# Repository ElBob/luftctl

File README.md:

# luftctl

Small ESP32-C3 controller board to power two 12V PWM fans from a single USB-C plug.

## hardware

Schematic and PCB design can be found in [`hardware/`](hardware/). It is a KiCAD 6 project.

The schematic is available as [a PDF](schematic.pdf).

For hand-soldering, you can use the [interactive BOM viewer](hardware/ibom.html).

## firmware

### micropython

The first simple test just loops through {`5V/off`, `5V/on`, `12V/off`, `12V/on`} with every button press.

Download MicroPython from [micropython.org/download/esp32c3-usb/](https://micropython.org/download/esp32c3-usb/) and flash it with:

```
esptool.py --chip esp32c3 --port /dev/ttyACM0 erase_flash
esptool.py --chip esp32c3 --port /dev/ttyACM0 --baud 460800 write_flash -z 0x0 esp32c3-*.bin
```

Then install a virtualenv with `adafruit-ampy` and upload the [`main.py`](main.py):

```
ampy -p /dev/ttyACM0 put main.py
ampy -p /dev/ttyACM0 reset --hard
```

The red LED will blink upon every state change.

### esphome

Since the ESP32-C3 is easily supported by ESPHome, you can also add it in your HomeAssistant automation using the [provided example YAML](esphome/luftctl.yaml).

## images

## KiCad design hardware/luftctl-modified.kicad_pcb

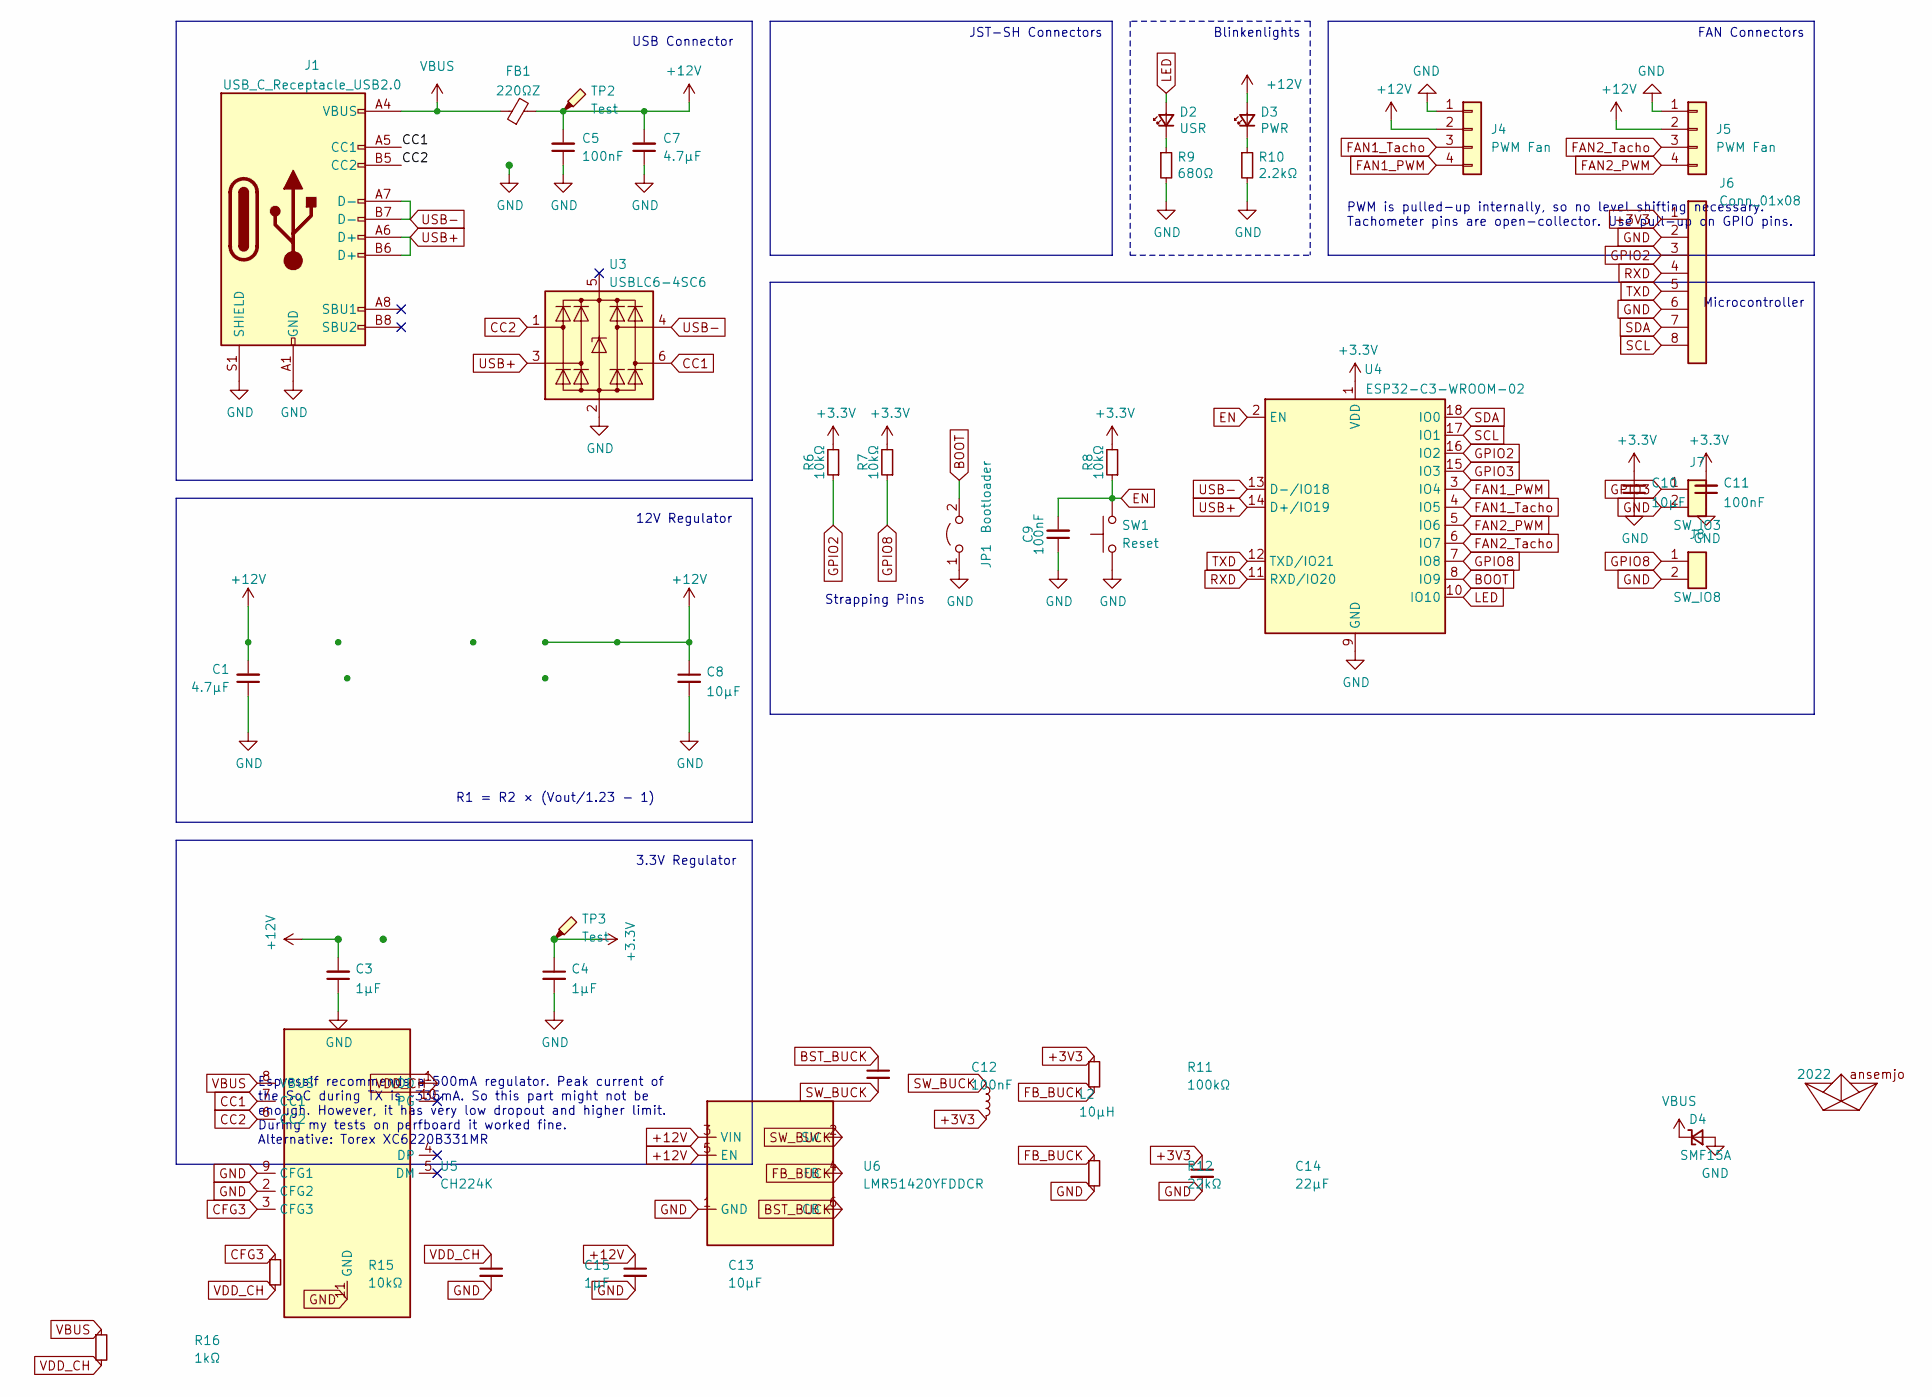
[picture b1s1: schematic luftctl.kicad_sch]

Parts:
A1: 2022; ahoi
C1, C7: 4.7µF; C_0805_2012Metric_Pad1.18x1.45mm_HandSolder
C3, C4, C15: 1µF; C_0805_2012Metric_Pad1.18x1.45mm_HandSolder
C5, C9, C11, C12: 100nF; C_0805_2012Metric_Pad1.18x1.45mm_HandSolder
C8, C10, C13: 10µF; C_0805_2012Metric_Pad1.18x1.45mm_HandSolder
C14: 22µF; C_0805_2012Metric_Pad1.18x1.45mm_HandSolder
D2: USR; LED_0805_2012Metric_Pad1.15x1.40mm_HandSolder
D3: PWR; LED_0805_2012Metric_Pad1.15x1.40mm_HandSolder
D4: SMF15A; D_SOD-123F
FB1: 220ΩZ; L_0805_2012Metric_Pad1.15x1.40mm_HandSolder
J1: USB_C_Receptacle_USB2.0; USB_C_Receptacle_HRO_TYPE-C-31-M-12
J4, J5: PWM Fan; FanPinHeader_1x04_P2.54mm_Vertical
J6: Conn_01x08; PinHeader_1x08_P2.54mm_Vertical
J7: SW_IO3; PinHeader_1x02_P2.54mm_Vertical
J8: SW_IO8; PinHeader_1x02_P2.54mm_Vertical
JP1: Bootloader; SW_SPST_TS-1088-xR020
L2: 10µH; L_Bourns_SRN6045TA
R6, R7, R8, R15: 10kΩ; R_0805_2012Metric_Pad1.20x1.40mm_HandSolder
R9: 680Ω; R_0805_2012Metric_Pad1.20x1.40mm_HandSolder
R10: 2.2kΩ; R_0805_2012Metric_Pad1.20x1.40mm_HandSolder
R11: 100kΩ; R_0805_2012Metric_Pad1.20x1.40mm_HandSolder
R12: 22kΩ; R_0805_2012Metric_Pad1.20x1.40mm_HandSolder
R16: 1kΩ; R_0805_2012Metric_Pad1.20x1.40mm_HandSolder
SW1: Reset; SW_SPST_TS-1088-xR020
TP2, TP3: Test; TestPoint_THTPad_D1.5mm_Drill0.7mm
U3: USBLC6-4SC6; SOT-23-6; MPN USBLC6-4SC6; Digi-Key_PN 497-4492-1-ND
U4: ESP32-C3-WROOM-02; ESP-WROOM-02
U5: CH224K; SSOP-10-1EP_3.9x4.9mm_P1mm_EP2.1x3.3mm
U6: LMR51420YFDDCR; SOT-23-6

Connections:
+12V: C1.2, C3.2, C5.2, C7.2, C8.1, C13.1, D3.2 (A), FB1.2, J4.2, J5.2, TP2.1, U6.3 (VIN), U6.5 (EN)
BOOT: JP1.2 (B), U4.8 (IO9)
BST_BUCK: C12.1, U6.6 (CB)
CC1: J1.A5 (CC1), U3.6 (I/O4), U5.7 (CC1)
CC2: J1.B5 (CC2), U3.1 (I/O1), U5.6 (CC2)
CFG3: R15.1, U5.3 (CFG3)
EN: C9.2, R8.1, SW1.2, U4.2 (EN)
FAN1_PWM: J4.4, U4.3 (IO4)
FAN1_Tacho: J4.3, U4.4 (IO5)
FAN2_PWM: J5.4, U4.5 (IO6)
FAN2_Tacho: J5.3, U4.6 (IO7)
FB_BUCK: R11.2, R12.1, U6.4 (FB)
GND: C1.1, C3.1, C4.2, C5.1, C7.1, C8.2, C9.1, C10.1, C11.1, C13.2, C14.2, C15.2, D4.2 (A), J1.A1 (GND), J1.A12 (GND), J1.B1 (GND), J1.B12 (GND), J1.S1 (SHIELD), J4.1, J5.1, J6.2, J6.6, J7.2, J8.2, JP1.1 (A), R9.2, R10.2, R12.2, SW1.1, U3.2 (GND), U4.9 (GND), U4.19 (GND), U5.2 (CFG2), U5.9 (CFG1), U5.11 (GND), U6.1 (GND)
GPIO2: J6.3, R6.1, U4.16 (IO2)
GPIO3: J7.1, U4.15 (IO3)
GPIO8: J8.1, R7.1, U4.7 (IO8)
LED: D2.2 (A), U4.10 (IO10)
unnamed: D2.1 (K), R9.1
unnamed: D3.1 (K), R10.1
RXD: J6.4, U4.11 (RXD/IO20)
SCL: J6.8, U4.17 (IO1)
SDA: J6.7, U4.18 (IO0)
SW_BUCK: C12.2, L2.1, U6.2 (SW)
TXD: J6.5, U4.12 (TXD/IO21)
USB+: J1.A6 (D+), J1.B6 (D+), U3.3 (I/O2), U4.14 (D+/IO19)
USB-: J1.A7 (D-), J1.B7 (D-), U3.4 (I/O3), U4.13 (D-/IO18)
VBUS: D4.1 (K), FB1.1, J1.A4 (VBUS), J1.A9 (VBUS), J1.B4 (VBUS), J1.B9 (VBUS), R16.1, U5.8 (VBUS)
VDD_CH: C15.1, R15.2, R16.2, U5.1 (VDD)

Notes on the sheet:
3.3V Regulator
PWM is pulled-up internally, so no level shifting necessary. Tachometer pins are open-collector. Use pull-up on GPIO pins.
12V Regulator
Strapping Pins
USB Connector
JST-SH Connectors
Microcontroller
FAN Connectors
R1 = R2 × (Vout/1.23 - 1)
Blinkenlights
Espressif recommends a 500mA regulator. Peak current of the SoC during TX is ~335mA. So this part might not be enough. However, it has very low dropout and higher limit. During my tests on perfboard it worked fine. Alternative: Torex XC6220B331MR

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
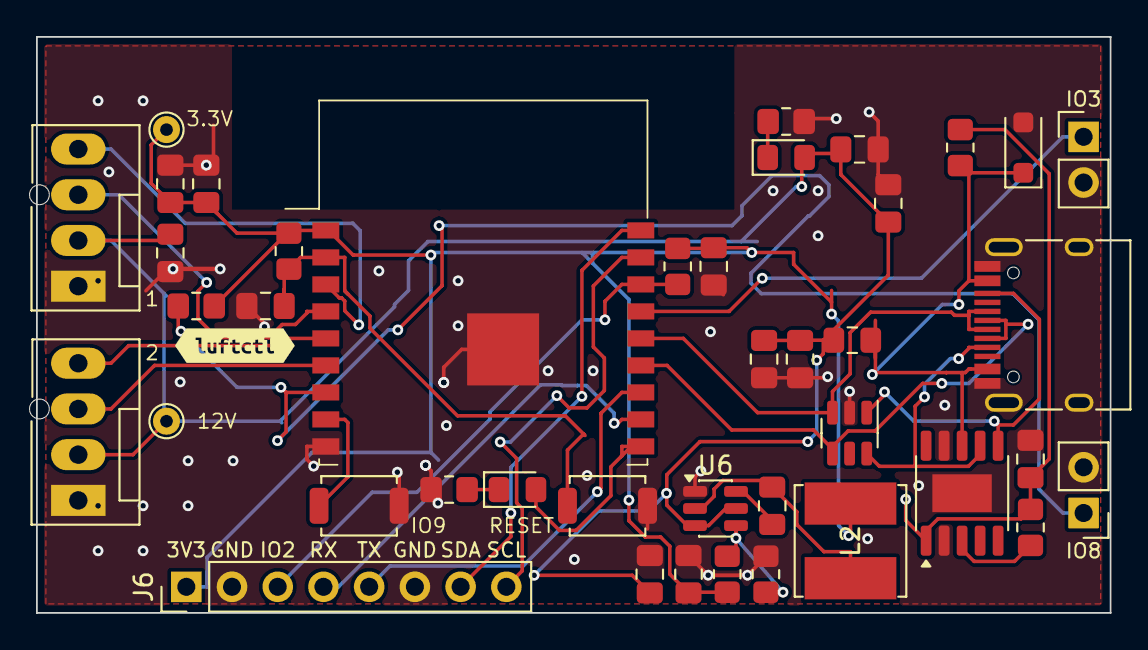
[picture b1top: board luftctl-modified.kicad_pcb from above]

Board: 2 copper layers, 59.7 x 32.0 mm, 42 parts (0 on the bottom side), 29 nets.

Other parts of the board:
kibuzzard-61E47F36: G***; kibuzzard-61E47F36

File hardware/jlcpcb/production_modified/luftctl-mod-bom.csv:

Comment,Designator,Footprint,LCSC Part #
4.7µF,"C1,C7",Capacitor_SMD:C_0805_2012Metric_Pad1.18x1.45mm_HandSolder,C1779
1µF,"C3,C4,C15",Capacitor_SMD:C_0805_2012Metric_Pad1.18x1.45mm_HandSolder,C28323
100nF,"C5,C9,C11,C12",Capacitor_SMD:C_0805_2012Metric_Pad1.18x1.45mm_HandSolder,C49678
10µF,"C8,C10,C13",Capacitor_SMD:C_0805_2012Metric_Pad1.18x1.45mm_HandSolder,C15850
22µF,C14,Capacitor_SMD:C_0805_2012Metric_Pad1.18x1.45mm_HandSolder,C45783
USR,D2,LED_SMD:LED_0805_2012Metric_Pad1.15x1.40mm_HandSolder,C84256
PWR,D3,LED_SMD:LED_0805_2012Metric_Pad1.15x1.40mm_HandSolder,C84256
SMF15A,D4,Diode_SMD:D_SOD-123F,C19077509
220ΩZ,FB1,Inductor_SMD:L_0805_2012Metric_Pad1.15x1.40mm_HandSolder,C85840
USB_C_Receptacle_USB2.0,J1,Connector_USB:USB_C_Receptacle_HRO_TYPE-C-31-M-12,C165948
Bootloader,JP1,Button_Switch_SMD:SW_SPST_TS-1088-xR020,C720477
10µH,L2,Inductor_SMD:L_Bourns_SRN6045TA,C2046332
10kΩ,"R6,R7,R8,R15",Resistor_SMD:R_0805_2012Metric_Pad1.20x1.40mm_HandSolder,C17414
680Ω,R9,Resistor_SMD:R_0805_2012Metric_Pad1.20x1.40mm_HandSolder,C17798
2.2kΩ,R10,Resistor_SMD:R_0805_2012Metric_Pad1.20x1.40mm_HandSolder,C17520
100kΩ,R11,Resistor_SMD:R_0805_2012Metric_Pad1.20x1.40mm_HandSolder,C149504
22kΩ,R12,Resistor_SMD:R_0805_2012Metric_Pad1.20x1.40mm_HandSolder,C17560
1kΩ,R16,Resistor_SMD:R_0805_2012Metric_Pad1.20x1.40mm_HandSolder,C17513
Reset,SW1,Button_Switch_SMD:SW_SPST_TS-1088-xR020,C720477
USBLC6-4SC6,U3,Package_TO_SOT_SMD:SOT-23-6,C6807798
ESP32-C3-WROOM-02-N4,U4,RF_Module:ESP-WROOM-02,C2934560
CH224K,U5,Package_SO:SSOP-10-1EP_3.9x4.9mm_P1mm_EP2.1x3.3mm,C970725
LMR51420YFDDCR,U6,Package_TO_SOT_SMD:SOT-23-6,C7296200

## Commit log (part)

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2026-01-25 add an esphome config yaml
2026-01-26 update readme and add esphome screenshot
